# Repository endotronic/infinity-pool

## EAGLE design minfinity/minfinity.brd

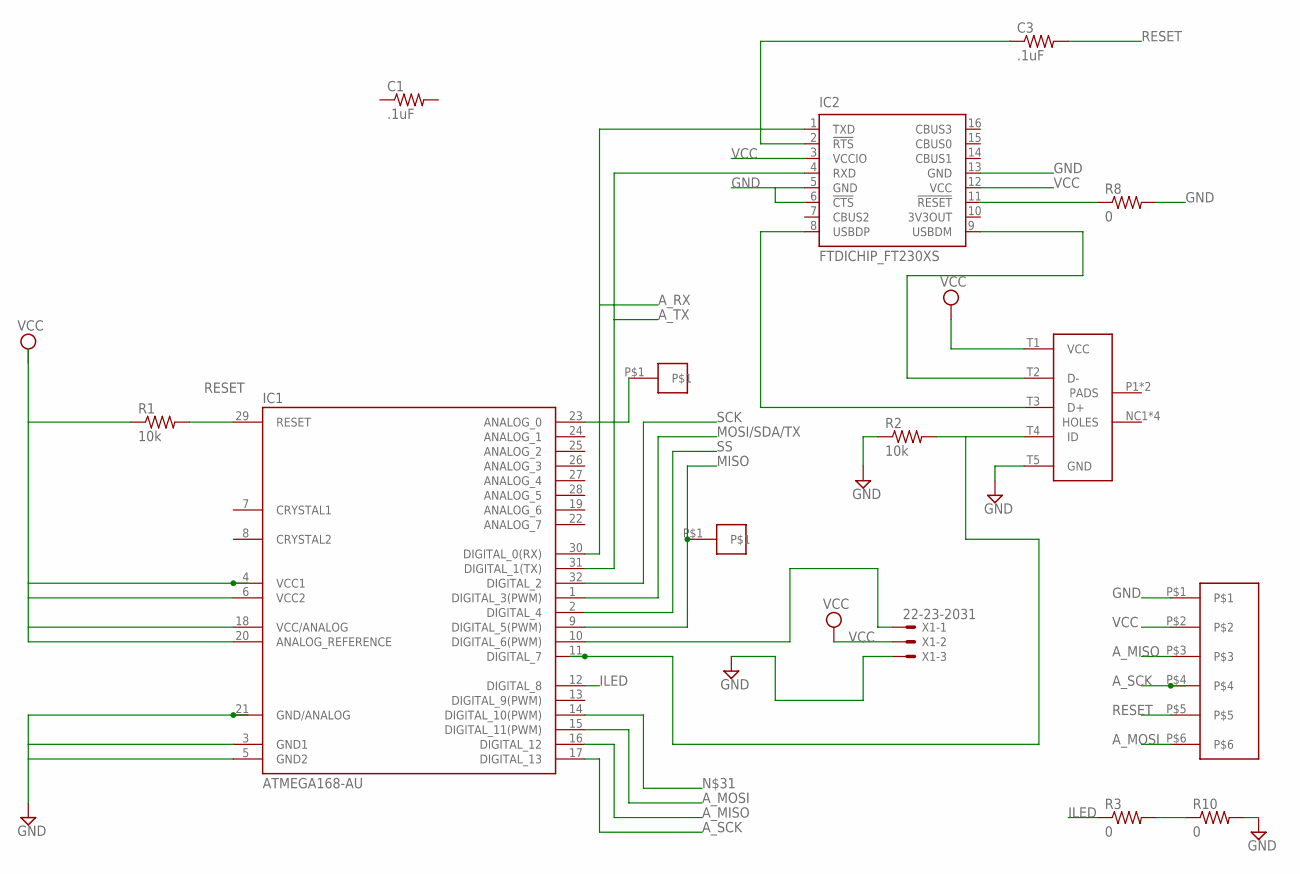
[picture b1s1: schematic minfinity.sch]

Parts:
C1, C3: .1uF; SUPERKEVIN_R0805
IC1: ATMEGA168-AU; TQFP32-08
IC2: FTDICHIP_FT230XS; FTDICHIP_SSOP16
R1, R2: 10k; SUPERKEVIN_R0805
R3, R8, R10: 0; SUPERKEVIN_R0805
U$1, U$16: TP
U$2: SUPERKEVIN_609-4049-1
U$7: RJ11; RJ11-SMT
X1: 22-23-2031

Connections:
A0: IC1.23 (ANALOG_0), U$16.P$1
A_MISO: IC1.16 (DIGITAL_12), U$7.P$3
A_MOSI: IC1.15 (DIGITAL_11(PWM)), U$7.P$6
A_RX: IC1.30 (DIGITAL_0(RX)), IC2.1 (TXD)
A_SCK: IC1.17 (DIGITAL_13), U$7.P$4
A_TX: IC1.31 (DIGITAL_1(TX)), IC2.4 (RXD)
GND: IC1.3 (GND1), IC1.5 (GND2), IC1.21 (GND/ANALOG), IC2.5 (GND), IC2.6 (!CTS), IC2.13 (GND), R2.1, R8.2, R10.2, U$2.T5 (GND), U$7.P$1, X1.3
ILED: IC1.12 (DIGITAL_8), R3.1
MISO: IC1.9 (DIGITAL_5(PWM)), U$1.P$1
MOSI/SDA/TX: IC1.1 (DIGITAL_3(PWM))
unnamed: IC2.9 (USBDM), U$2.T2 (D-)
unnamed: IC1.10 (DIGITAL_6(PWM)), X1.1
unnamed: IC1.11 (DIGITAL_7), R2.2, U$2.T4 (ID)
unnamed: IC2.8 (USBDP), U$2.T3 (D+)
unnamed: IC2.11 (!RESET), R8.1
unnamed: R3.2, R10.1
unnamed: C3.1, IC2.2 (!RTS)
RESET: C3.2, IC1.29 (RESET), R1.2, U$7.P$5
SCK: IC1.32 (DIGITAL_2)
SS: IC1.2 (DIGITAL_4)
VCC: IC1.4 (VCC1), IC1.6 (VCC2), IC1.18 (VCC/ANALOG), IC1.20 (ANALOG_REFERENCE), IC2.3 (VCCIO), IC2.12 (VCC), R1.1, U$2.T1 (VCC), U$7.P$2, X1.2

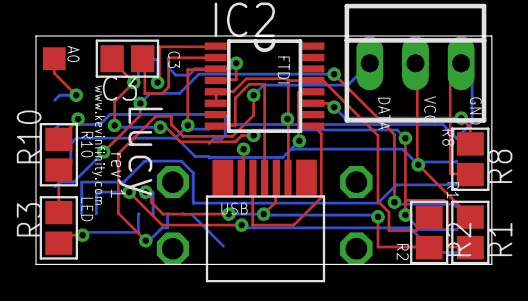
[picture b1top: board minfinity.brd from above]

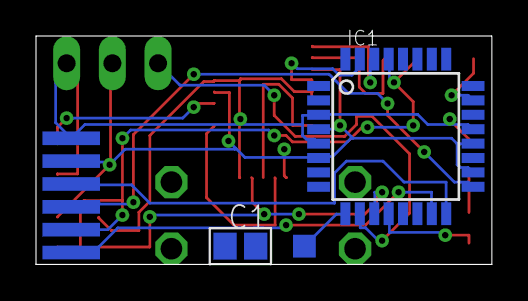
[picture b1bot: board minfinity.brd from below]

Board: 2 copper layers, 25.3 x 12.7 mm, 14 parts (4 on the bottom side), 18 nets.

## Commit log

2014-07-10 Prototype code
2014-07-10 Use less RAM
2014-07-12 Small pool is working
2014-07-13 Added support for multiple strips (large pool)
2014-07-14 Fix ports
2014-07-26 Add minfinity and fix memory bug
2014-07-26 Add laser cuts
2014-07-31 Update cuts
